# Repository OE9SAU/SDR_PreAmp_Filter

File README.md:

## V2.0 Signalrichtung angepasst, LPF-Filter ist jetzt vor dem PRE-AMP

# Kompakter LNA mit integriertem 5-stufigem Tiefpassfilter 
**basierend auf dem LTC6226xS8, mit integriertem 5-fach-Tiefpassfilter für den Bereich 1–30 MHz.**
**Die Filterumschaltung erfolgt mit drei Steuerleitungen und zwei 74CBT3251-Multiplexer. Ausgangspegel ca. 10–12 dBm – für SDRs und andere Empfänger.**

*Compact LNA using an LTC6226xS8 amplifier with integrated 5-way low-pass filtering for the 1–30 MHz range.*
*Filter selection is handled via 3-bit control (A0–A2) and two 74CBT3251 multiplexers. Output level approx. 10–12 dBm – for SDRs and similar receivers.*

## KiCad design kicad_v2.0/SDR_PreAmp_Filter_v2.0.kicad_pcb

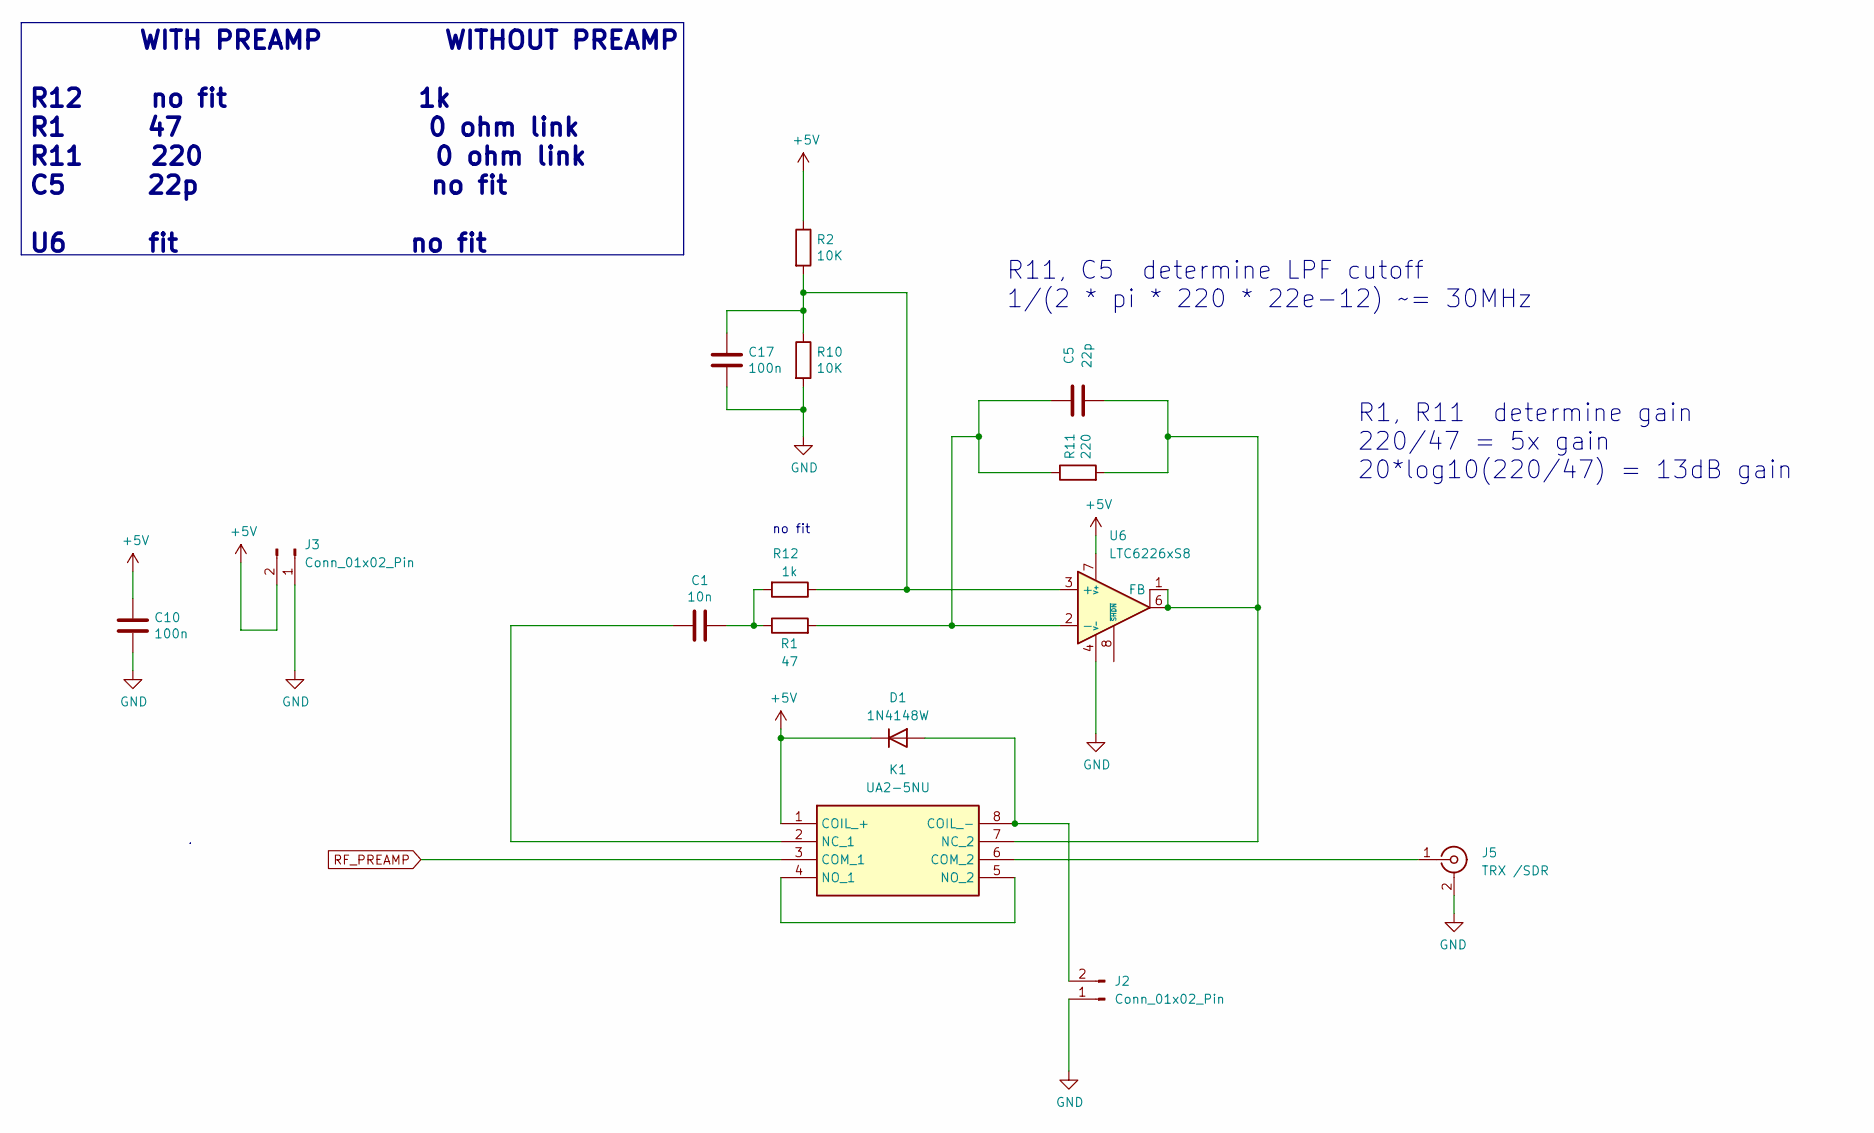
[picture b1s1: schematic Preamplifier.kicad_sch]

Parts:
C1: 10n; C_0805_2012Metric
C5: 22p; C_0805_2012Metric
C10, C17: 100n; C_0805_2012Metric
D1: 1N4148W; D_0805_2012Metric_Pad1.15x1.40mm_HandSolder
J2, J3: Conn_01x02_Pin; PinHeader_1x02_P2.54mm_Vertical
J5: TRX /SDR; SMA_Samtec_SMA-J-P-X-ST-EM1_EdgeMount
K1: UA2-5NU; UA245NJ; Manufacturer_Part_Number UA2-5NU; Mouser Part Number 80-UA2-5NU
R1: 47; R_0805_2012Metric
R2, R10: 10K; R_0805_2012Metric
R11: 220; R_0805_2012Metric
R12: 1k; R_0805_2012Metric
U6: LTC6226xS8; SO-8_3.9x4.9mm_P1.27mm

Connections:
+5V: C10.1, D1.1 (K), J3.2, K1.1 (COIL_+), R2.1, U6.7 (V+); also elsewhere on the board
GND: C10.2, C17.2, J2.1, J3.1, J5.2 (Ext), R10.2, U6.4 (V-), U6.5 (V-); also elsewhere on the board
unnamed: C1.1, R1.1, R12.2
unnamed: D1.2 (A), J2.2, K1.8 (COIL_-)
unnamed: J5.1 (In), K1.6 (COM_2)
unnamed: C1.2, K1.2 (NC_1)
unnamed: C5.2, K1.7 (NC_2), R11.2, U6.1 (FB), U6.6
unnamed: K1.4 (NO_1), K1.5 (NO_2)
unnamed: C17.1, R2.2, R10.1, R12.1, U6.3 (+)
unnamed: C5.1, R1.2, R11.1, U6.2 (-)
RF_PREAMP: K1.3 (COM_1); also elsewhere on the board

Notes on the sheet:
no fit
R11, C5 determine LPF cutoff 1/(2 * pi * 220 * 22e-12) ~= 30MHz
R1, R11 determine gain 220/47 = 5x gain 20*log10(220/47) = 13dB gain
WITH PREAMP WITHOUT PREAMP R12 no fit 1k R1 47 0 ohm link R11 220 0 ohm link C5 22p no fit U6 fit no fit

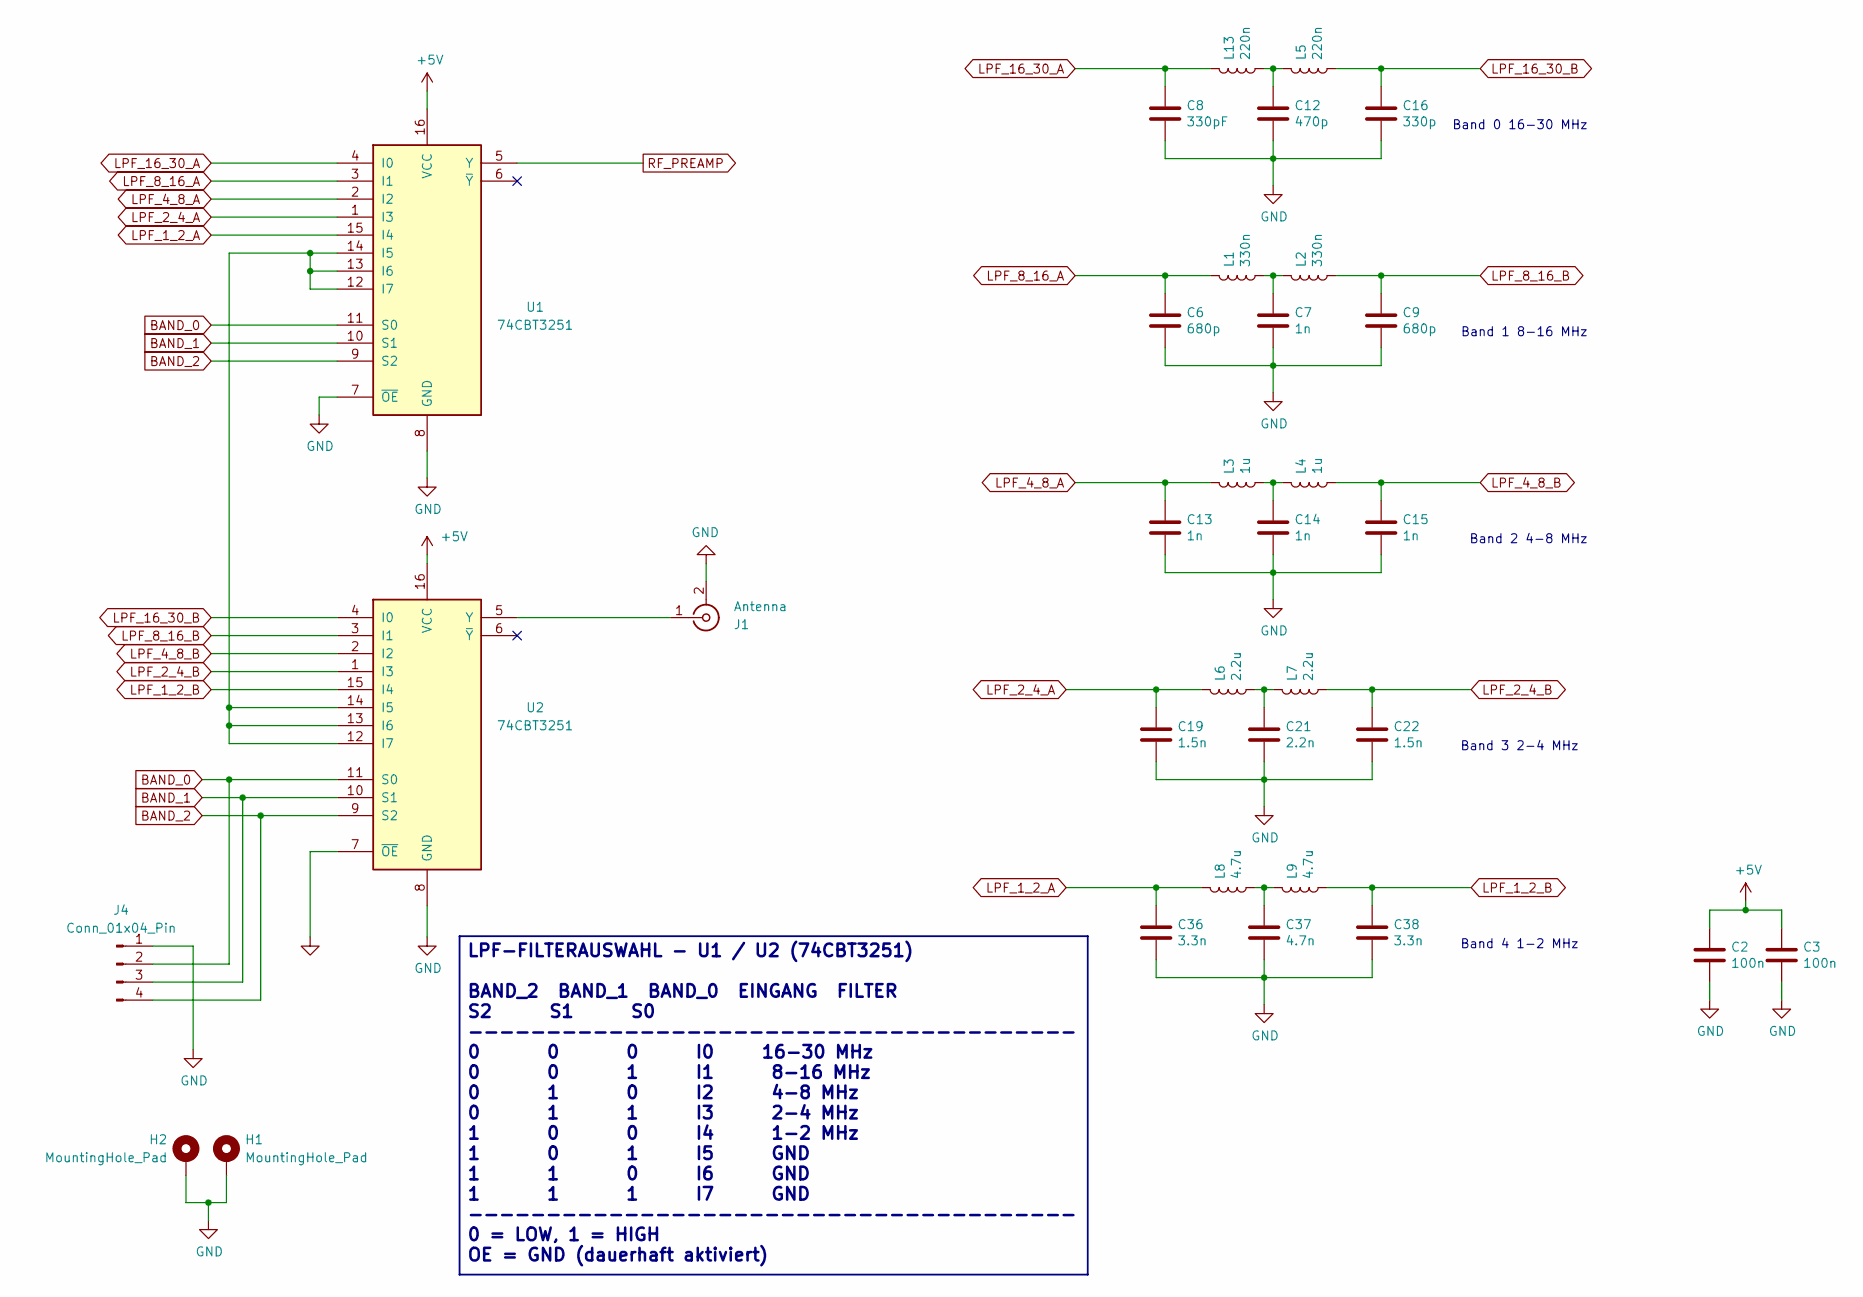
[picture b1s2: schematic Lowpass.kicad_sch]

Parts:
C2, C3: 100n; C_0805_2012Metric
C6, C9: 680p; C_0805_2012Metric
C7, C13, C14, C15: 1n; C_0805_2012Metric
C8: 330pF; C_0805_2012Metric
C12: 470p; C_0805_2012Metric
C16: 330p; C_0805_2012Metric
C19, C22: 1.5n; C_0805_2012Metric
C21: 2.2n; C_0805_2012Metric
C36, C38: 3.3n; C_0805_2012Metric
C37: 4.7n; C_0805_2012Metric
H1, H2: MountingHole_Pad; MountingHole_3.2mm_M3_DIN965_Pad
J1: Antenna; SMA_Samtec_SMA-J-P-X-ST-EM1_EdgeMount
J4: Conn_01x04_Pin; PinHeader_1x04_P2.54mm_Vertical
L1, L2: 330n; L_0805_2012Metric_Pad1.05x1.20mm_HandSolder
L3, L4: 1u; L_0805_2012Metric_Pad1.05x1.20mm_HandSolder
L5, L13: 220n; L_0805_2012Metric_Pad1.05x1.20mm_HandSolder
L6, L7: 2.2u; L_0805_2012Metric_Pad1.05x1.20mm_HandSolder
L8, L9: 4.7u; L_0805_2012Metric_Pad1.05x1.20mm_HandSolder
U1, U2: 74CBT3251; SOIC-16_3.9x9.9mm_P1.27mm

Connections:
+5V: C2.1, C3.1, U1.16 (VCC), U2.16 (VCC); also elsewhere on the board
BAND_0: J4.2, U1.11 (S0), U2.11 (S0)
BAND_1: J4.3, U1.10 (S1), U2.10 (S1)
BAND_2: J4.4, U1.9 (S2), U2.9 (S2)
GND: C2.2, C3.2, C6.1, C7.1, C8.1, C9.1, C12.1, C13.1, C14.1, C15.1, C16.1, C19.1, C21.1, C22.1, C36.1, C37.1, C38.1, H1.1, H2.1, J1.2 (Ext), J4.1, U1.7 (~OE), U1.8 (GND), U2.7 (~OE), U2.8 (GND); also elsewhere on the board
LPF_1_2_A: C36.2, L8.2, U1.15 (I4)
LPF_1_2_B: C38.2, L9.1, U2.15 (I4)
LPF_2_4_A: C19.2, L6.2, U1.1 (I3)
LPF_2_4_B: C22.2, L7.1, U2.1 (I3)
LPF_4_8_A: C13.2, L3.2, U1.2 (I2)
LPF_4_8_B: C15.2, L4.1, U2.2 (I2)
LPF_8_16_A: C6.2, L1.2, U1.3 (I1)
LPF_8_16_B: C9.2, L2.1, U2.3 (I1)
LPF_16_30_A: C8.2, L13.2, U1.4 (I0)
LPF_16_30_B: C16.2, L5.1, U2.4 (I0)
unnamed: C7.2, L1.1, L2.2
unnamed: C12.2, L5.2, L13.1
unnamed: C14.2, L3.1, L4.2
unnamed: C21.2, L6.1, L7.2
unnamed: C37.2, L8.1, L9.2
unnamed: J1.1 (In), U2.5 (Y)
unnamed: U1.12 (I7), U1.13 (I6), U1.14 (I5), U2.12 (I7), U2.13 (I6), U2.14 (I5)
RF_PREAMP: U1.5 (Y); also elsewhere on the board

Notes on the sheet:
Band 2 4-8 MHz
Band 4 1-2 MHz
Band 1 8-16 MHz
Band 3 2-4 MHz
Band 0 16-30 MHz
LPF-FILTERAUSWAHL - U1 / U2 (74CBT3251) BAND_2 BAND_1 BAND_0 EINGANG FILTER S2 S1 S0 --------------------------------------- 0 0 0 I0 16-30 MHz 0 0 1 I1 8-16 MHz 0 1 0 I2 4-8 MHz 0 1 1 I3 2-4 MHz 1 0 0 I4 1-2 MHz 1 0 1 I5 GND 1 1 0 I6 GND 1 1 1 I7 GND --------------------------------------- 0 = LOW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

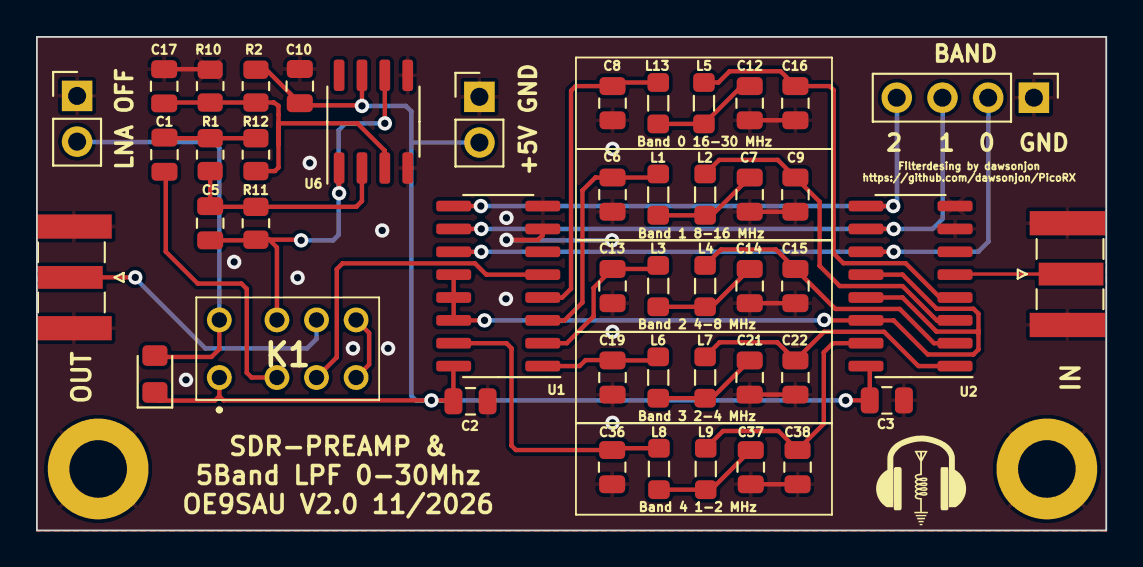
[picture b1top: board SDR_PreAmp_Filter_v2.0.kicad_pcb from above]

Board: 2 copper layers, 59.4 x 27.4 mm, 50 parts (1 on the bottom side), 31 nets.

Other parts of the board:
G0, G1: LOGO

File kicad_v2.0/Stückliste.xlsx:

Reference | Value | Datasheet | Footprint | Qty | DNP
C1 | 10n | ~ | Capacitor_SMD:C_0805_2012Metric | 1
C2,C3,C10,C17 | 100n | ~ | Capacitor_SMD:C_0805_2012Metric | 4
C5 | 22p | ~ | Capacitor_SMD:C_0805_2012Metric | 1
C6,C9 | 680p | ~ | Capacitor_SMD:C_0805_2012Metric | 2
C7,C13,C14,C15 | 1n | ~ | Capacitor_SMD:C_0805_2012Metric | 4
C8 | 330pF | ~ | Capacitor_SMD:C_0805_2012Metric | 1
C12 | 470p | ~ | Capacitor_SMD:C_0805_2012Metric | 1
C16 | 330p | ~ | Capacitor_SMD:C_0805_2012Metric | 1
C19,C22 | 1.5n | ~ | Capacitor_SMD:C_0805_2012Metric | 2
C21 | 2.2n | ~ | Capacitor_SMD:C_0805_2012Metric | 1
C36,C38 | 3.3n | ~ | Capacitor_SMD:C_0805_2012Metric | 2
C37 | 4.7n | ~ | Capacitor_SMD:C_0805_2012Metric | 1
J2 | LNA_OUT |  | 60314202124525:60314202124525 | 1
J5 | Antenna | ~ | Connector_Coaxial:SMA_Samtec_SMA-J-P-X-ST-EM1_EdgeMount | 1
L1,L2 | 330n | ~ | Inductor_SMD:L_0805_2012Metric_Pad1.05x1.20mm_HandSolder | 2
L3,L4 | 1u | ~ | Inductor_SMD:L_0805_2012Metric_Pad1.05x1.20mm_HandSolder | 2
L5,L13 | 220n | ~ | Inductor_SMD:L_0805_2012Metric_Pad1.05x1.20mm_HandSolder | 2
L6,L7 | 2.2u | ~ | Inductor_SMD:L_0805_2012Metric_Pad1.05x1.20mm_HandSolder | 2
L8,L9 | 4.7u | ~ | Inductor_SMD:L_0805_2012Metric_Pad1.05x1.20mm_HandSolder | 2
R1 | 47 | ~ | Resistor_SMD:R_0805_2012Metric | 1
R2,R10 | 10K | ~ | Resistor_SMD:R_0805_2012Metric | 2
R11 | 220 | ~ | Resistor_SMD:R_0805_2012Metric | 1
R12 | 1k | ~ | Resistor_SMD:R_0805_2012Metric | 1
U1,U2 | 74CBT3251 | http://www.ti.com/lit/gpn/sn74LS251 | Package_SO:SOIC-16_3.9x9.9mm_P1.27mm | 2
U6 | LTC6226xS8 | https://www.analog.com/media/en/technical-documentation/data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 | Package_SO:SO-8_3.9x4.9mm_P1.27mm | 1

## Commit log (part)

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2025-05-23 Update_OE9SAU
2025-05-27 Update PCB
2025-05-28 PCB Update
2025-05-28 PCB_Update
2025-06-10 Commits
2025-06-10 Commit pcb
2025-06-10 Via Update
2025-06-10 Pic update
2025-07-17 v1.1
2025-07-17 v.1.1
